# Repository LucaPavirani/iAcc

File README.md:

# Electronic Technologies and Biosensors Laboratory

## Academic Year 2021/2022 - II Semester

## Final Project - Project 4 - Respiratory/Heart Rate Monitor

## Objective

In this project, the aim was to develop a simple **Respiratory/Heart Rate Monitor** based on the PSoC and a 3-axis accelerometer LIS3DH. The device implements an algorithm for respiratory and heart rate computation, and then it allows data visualization on a custom GUI. PSOC and PC communication relies on a HC-05 BT Module either to make the device wearable and to reduce the cable bulkyness.
The PSoC communicates with the LIS3DH thanks to I2C communication, to acquire data at the best full-scale range possible, which has been set to $\pm 2G$, and with sampling frequency of 50 Hz.  
Finally, the whole PCB is powered thanks to a 9V battery, which allows the device to be portable and light. 

In the following image, the device is shown: 

## Repository structure

### Design files

This folder contains all the projects used to model and 3D print the case and the chest mount for the sensor, along with the Eagle files, used to design the PCB. 

### Documentation

This folder contains the literature analysed during the development of the project, while the *Datasheets* folder contains all the datasheets for the components with some other useful files. 

### GUI

The GUI folder contains all the files necessary to run the graphical interface, which is the following:

The *device search* button enables the automatic scan of all the serial ports, looking for the device. As soon as it finds it, the connection is established and the box on the right becomes green, confirming the operation. The *combobox* allows to choose to read both HR and RR or only one of them. Calibration must be performed the first time that the device is worn, so that the algorithm computes the proper threshold to detect the rates. Once calibration is over (1 min approx.), the algorithm starts to accumulate data and to calculate the peaks from the signal, in order to compute RR and HR.

The *file* button allows to export the data in a `.csv` file. This operation will be automatically performed if the device is suddenly disconnected, so that the data is not lost. 

Heart Rate and Respiratory Rate are computed on non overlapping recording windows of 30s. Raw data are filtered and analysed in two different way for the computation of the rates. 

### Heart Rate computation

First, the absolute value of recorded data is filtered by a butter bandpass filter of the 4th order with frequency range in [1 ,5]Hz. The resulting signal is then smoothed first by a Savitzky-Golay filter of the 3rd order with window length of 15 samples and then by a moving average. These steps provide a resulting waveform that crearly shows the heart beats while being quite robust against noise.  
The next step provides the threshold as the 80% of the average of the data. The algorithm looks for the peaks above the calculated threshold that are at least 25 samples apart, that correspond to 0.5s approx.  
Finally, the Heart Rate is computed as the fraction between the number of peaks in the recorded window and the length of the window in seconds. This value is updated every 30s approx.

### Respiratory Rate computation

The computation of the Respiratory Rate requires different filtering of the signal.  
First, recorded data go through a butter lowpass filter of the 5th orded with cutoff frequency of 3Hz. This filtered signal is then smoothed by a Savitzky-Golay filter with a window of 31 samples and 3rd order. The threshold is calculated in the same way as in the HR computation, but the peaks are searched every 50 samples. 
The Respiratory Rate is calculated in the same way as the Heart Rate.

### Images

Images used for this `readme` file.

### PSoC

The *PSoC Code* folder contains all the files used to program the PSoC: in particular, all the functions and variables have been reordered in the proper file, allowing to increase the main.c file readibility.  
This code basically sets the proper configuration for the accelerometer registers at startup, making it ready for the data acquisition. All the different phases are managed thanks to a UART, that enables the different operations, according to the signals that come from the GUI. So, at the beginning the accelerometer is set and ready, once the PSoC receives the *start* signal from the GUI it begins to acquire data and to transmit them.  

Regarding the data acquisition, as previously mentioned the accelerometer has been set to a sampling frequency of 50 Hz, according to the Shannon's theorem and to the literature. In addition to that, the accelerometer operates in **FIFO mode**, so it accumulates all the samplings in the FIFO register (which contains up to 32 samples) and then it stops getting new data until the register has been emptied, allowing to reduce the computational load on the CPU and so the battery consumption, with respect to **bypass** mode, that sends the data in a continuous stream.  
In order to read the FIFO register, the PSoC checks regularly the value of the *overrun bit*, that becomes 1 once the FIFO register is full and returns to 0 when it has been entirely read.  
Once the `ovrn bit` changes to one, the register is entirely read, storing the data in the respective axis array. Then, the data is packed in one single array and sent via UART.

*Further implementation details can be found in each file.*

## Complete hardware list

- 1 PSoC CY8CKIT-059 
- 1 LIS3DH accelerometer
- 1 HC05 Bluetooth module
- 1 9V battery
- 1 9V to 5V voltage regulator 
- 6 cables for the accelerometer-PSoC communication

## How to wear the device

The 3D files for the case and the support can be found in the Design folder.

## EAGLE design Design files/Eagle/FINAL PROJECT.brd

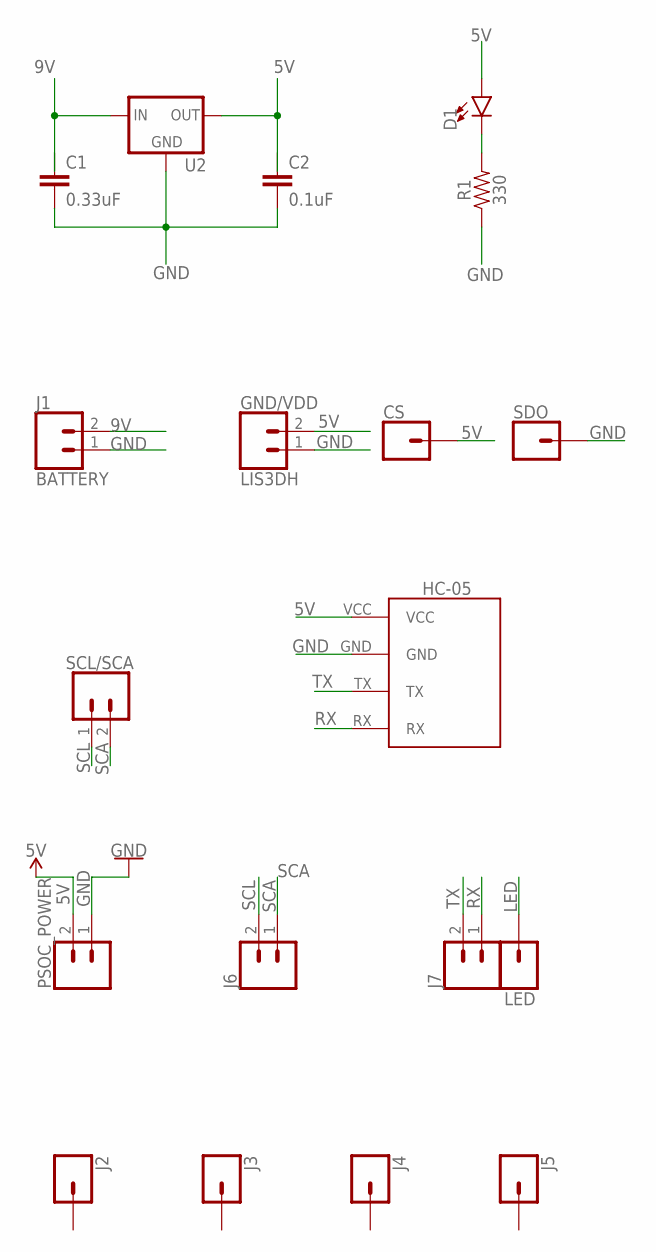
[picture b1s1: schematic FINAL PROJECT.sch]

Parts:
C1: 0.33uF; CAP-PTH-SMALL-KIT
C2: 0.1uF; CAP-PTH-SMALL-KIT
CS: CONN_01; 1X01
D1: LED3MM; LED_3MM
GND/VDD: LIS3DH; 1X02
HC-05: BLUETOOTH_BOARD; BT_BOARD_FOOTPRINT
J1: BATTERY; 1X02
J2, J3, J4, J5: CONN_01; 1X01
J6, J7: CONN_02; 1X02
LED: CONN_01; 1X01
PSOC_POWER: CONN_02; 1X02
R1: 330; AXIAL-0.3
SCL/SCA: CONN_02; 1X02
SDO: CONN_01; 1X01
U2: V_REG_78XX-TO-220; TO-220-ALT

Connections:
5V: C2.1, CS.1, D1.A, GND/VDD.2, HC-05.VCC, PSOC_POWER.2, U2.OUT
9V: C1.1, J1.2, U2.IN
GND: C1.2, C2.2, GND/VDD.1, HC-05.GND, J1.1, PSOC_POWER.1, R1.P$1 (1), SDO.1, U2.GND
LED: LED.1
unnamed: D1.K (C), R1.P$2 (2)
RX: HC-05.RX, J7.1
SCA: J6.1, SCL/SCA.2
SCL: J6.2, SCL/SCA.1
TX: HC-05.TX, J7.2

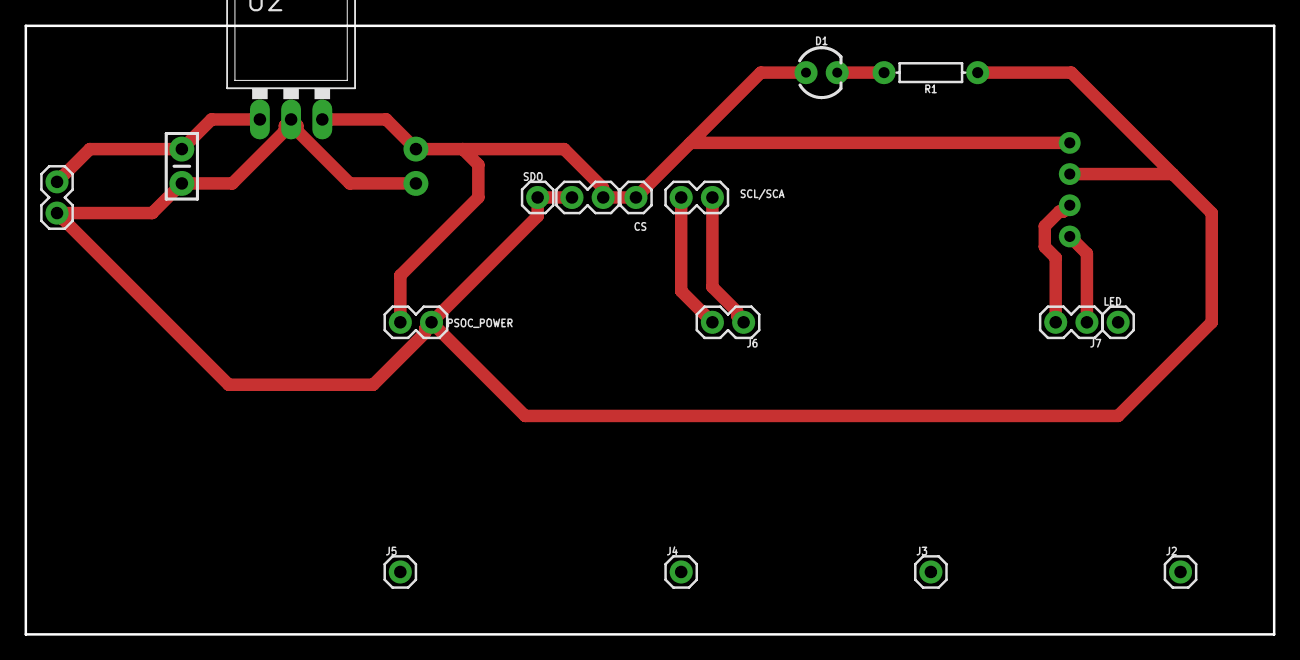
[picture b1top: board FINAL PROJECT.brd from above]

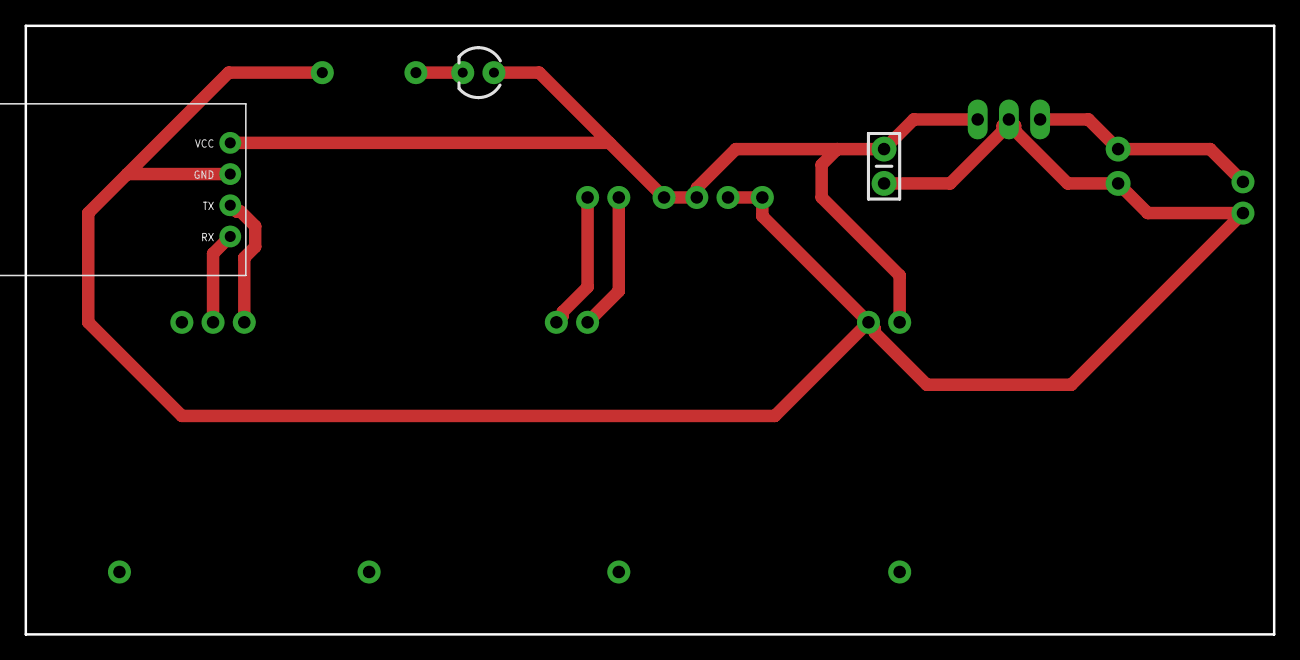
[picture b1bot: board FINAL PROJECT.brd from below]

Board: 2 copper layers, 101.6 x 49.5 mm, 19 parts (2 on the bottom side), 8 nets.

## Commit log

2022-07-13 iAcc
2022-07-13 Last updates

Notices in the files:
parts and their libraries:
SparkFun-IC-Power: Licensing: Creative Commons ShareAlike 4.0 International - https://creativecommons.org/licenses/by-sa/4.0
